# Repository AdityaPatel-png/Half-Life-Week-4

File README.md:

# Half-Life-Week-4
This project will be a projector that works similar to an external monitor.
In that, I mean that it will connect using an hdmi/display port cable and it will be compatible with most computer devices.
It will use a pcb to control the heatsink system since I found an LCD panel that has premapped settings to function as a monitor.
For the projectering I will use a very bright light with a heat blocking glass in front and make it pass through a 2k lcd panel.
I'll make a big space for a heatsink in the case as well as all of the dials and levers that the average projector has.
Most of the holes on the projector will just be tapped with a hand drill and a threaded insert will be fitted in.
Main resources used: KiCad and Fusion360

PCB Photos:

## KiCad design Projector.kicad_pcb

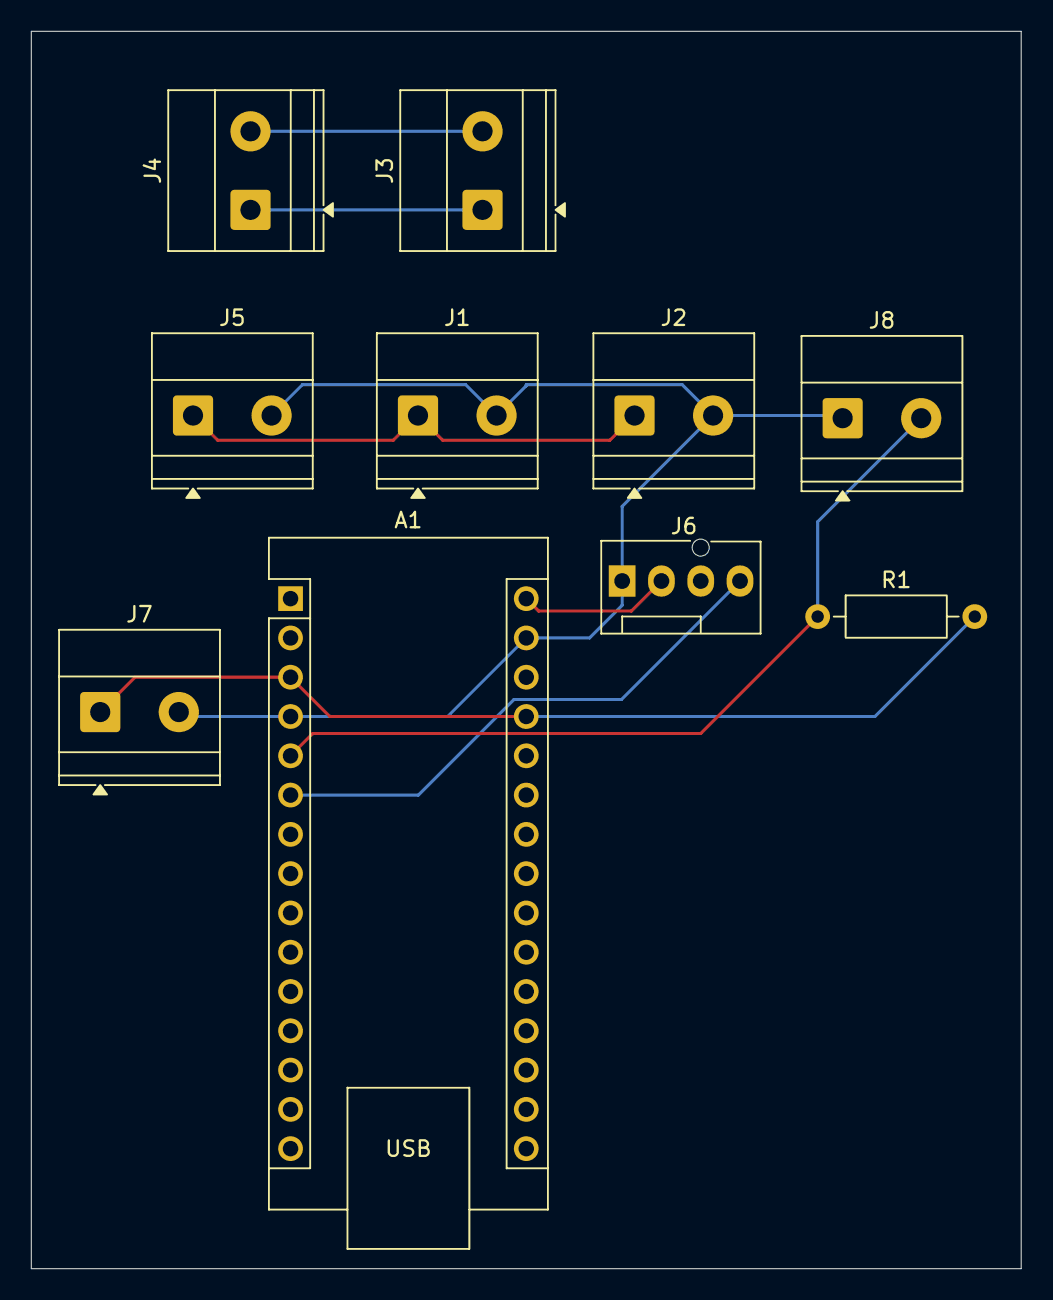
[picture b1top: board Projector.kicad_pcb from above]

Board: 2 copper layers, 64.0 x 80.0 mm, 10 parts (0 on the bottom side), 8 nets.

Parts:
A1: Arduino_Nano_v3.x; Arduino_Nano
J1: MAIN_IN; TerminalBlock_Phoenix_MKDS-1,5-2-5.08_1x02_P5.08mm_Horizont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
J2: DRIVER_IN; TerminalBlock_Phoenix_MKDS-1,5-2-5.08_1x02_P5.08mm_Horizont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
J3: DRIVER_OUT; TerminalBlock_Phoenix_MKDS-1,5-2-5.08_1x02_P5.08mm_Horizont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
J4: TO_LED_PANEL; TerminalBlock_Phoenix_MKDS-1,5-2-5.08_1x02_P5.08mm_Horizont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
J5: BUCK_INPUT; TerminalBlock_Phoenix_MKDS-1,5-2-5.08_1x02_P5.08mm_Horizont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
J6: Conn_01x04_Socket; FanPinHeader_1x04_P2.54mm_Vertical
J7: 5V_HDMI_BOARD_POWER; TerminalBlock_Phoenix_MKDS-1,5-2-5.08_1x02_P5.08mm_Horizont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
J8: TEMP_SENSOR_INPUT; TerminalBlock_Phoenix_MKDS-1,5-2-5.08_1x02_P5.08mm_Horizont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
R1: 4.7k; R_Axial_DIN0207_L6.3mm_D2.5mm_P10.16mm_Horizontal

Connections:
+5V: A1.3 (~RESET), A1.27 (+5V), J7.1, R1.2
+12V: A1.30 (VIN), J6.2
/19V: J1.1, J2.1, J5.1
/FAN_PWM: A1.6 (D3), J6.4
/LED_NEG: J3.2, J4.2
/LED_POS: J3.1, J4.1
/TEMP_DATA: A1.5 (D2), J8.2, R1.1
GND: A1.4 (GND), A1.29 (GND), J1.2, J2.2, J5.2, J6.1, J7.2, J8.1
